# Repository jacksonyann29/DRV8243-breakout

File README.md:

# DRV8243-breakout
 Twin Breakout Board for the Texas Instruments DRV8243 H-bridge Driver intended for driving 2 brushed DC motors.

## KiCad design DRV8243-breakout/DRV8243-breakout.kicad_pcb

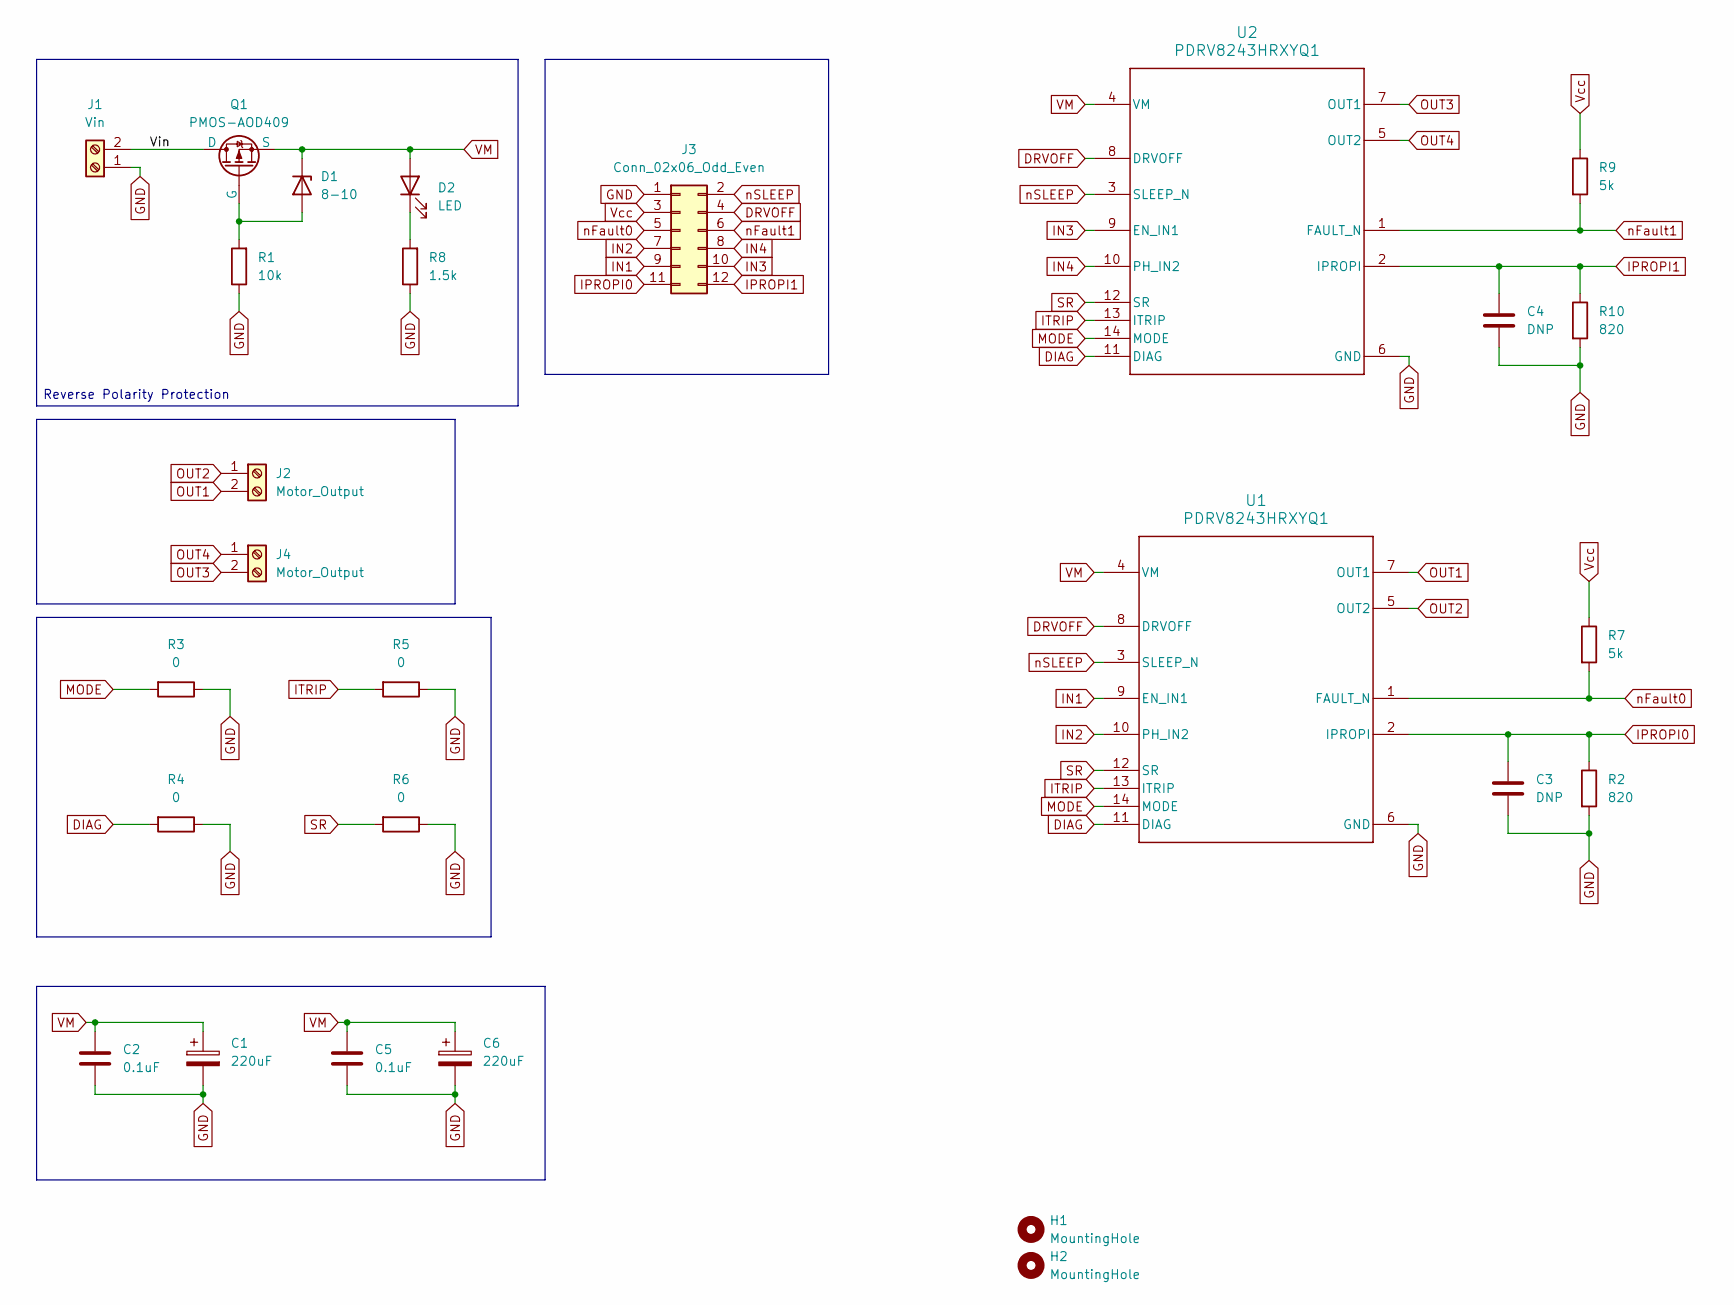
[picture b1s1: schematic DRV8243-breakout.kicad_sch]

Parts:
C1, C6: 220uF; CP_Elec_8x10.5
C2, C5: 0.1uF; C_0603_1608Metric
C3, C4: DNP; C_0805_2012Metric
D1: 8-10; D_SOD-123
D2: LED; LED_0805_2012Metric
H1, H2: MountingHole; MountingHole_3.2mm_M3
J1: Vin; TerminalBlock_Phoenix_MKDS-1,5-2_1x02_P5.00mm_Horizontal
J2, J4: Motor_Output; TerminalBlock_Phoenix_MKDS-1,5-2_1x02_P5.00mm_Horizontal
J3: Conn_02x06_Odd_Even; PinHeader_1x11_P2.54mm_Vertical
Q1: PMOS-AOD409; TO-252-2(DPAK)
R1: 10k; R_0805_2012Metric
R2, R10: 820; R_0805_2012Metric
R3, R4, R5, R6: 0; R_0805_2012Metric
R7, R9: 5k; R_0805_2012Metric
R8: 1.5k; R_0805_2012Metric
U1, U2: PDRV8243HRXYQ1; RXY0014A-MFG

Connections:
/Vin: J1.2, Q1.1 (D)
DIAG: R4.2, U1.11 (DIAG), U2.11 (DIAG)
DRVOFF: J3.4, U1.8 (DRVOFF), U2.8 (DRVOFF)
GND: C1.2, C2.2, C3.2, C4.2, C5.2, C6.2, J1.1, J3.1, R1.1, R2.2, R3.1, R4.1, R5.1, R6.1, R8.1, R10.2, U1.6 (GND), U2.6 (GND)
IN1: J3.9, U1.9 (EN_IN1)
IN2: J3.7, U1.10 (PH_IN2)
IN3: J3.10, U2.9 (EN_IN1)
IN4: J3.8, U2.10 (PH_IN2)
IPROPI0: C3.1, J3.11, R2.1, U1.2 (IPROPI)
IPROPI1: C4.1, J3.12, R10.1, U2.2 (IPROPI)
ITRIP: R5.2, U1.13 (ITRIP), U2.13 (ITRIP)
MODE: R3.2, U1.14 (MODE), U2.14 (MODE)
unnamed: D1.2 (A), Q1.2 (G), R1.2
unnamed: D2.1 (K), R8.2
OUT1: J2.2, U1.7 (OUT1)
OUT2: J2.1, U1.5 (OUT2)
OUT3: J4.2, U2.7 (OUT1)
OUT4: J4.1, U2.5 (OUT2)
SR: R6.2, U1.12 (SR), U2.12 (SR)
VM: C1.1, C2.1, C5.1, C6.1, D1.1 (K), D2.2 (A), Q1.3 (S), U1.4 (VM), U2.4 (VM)
Vcc: J3.3, R7.1, R9.1
nFault0: J3.5, R7.2, U1.1 (FAULT_N)
nFault1: J3.6, R9.2, U2.1 (FAULT_N)
nSLEEP: J3.2, U1.3 (SLEEP_N), U2.3 (SLEEP_N)

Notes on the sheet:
Reverse Polarity Protection

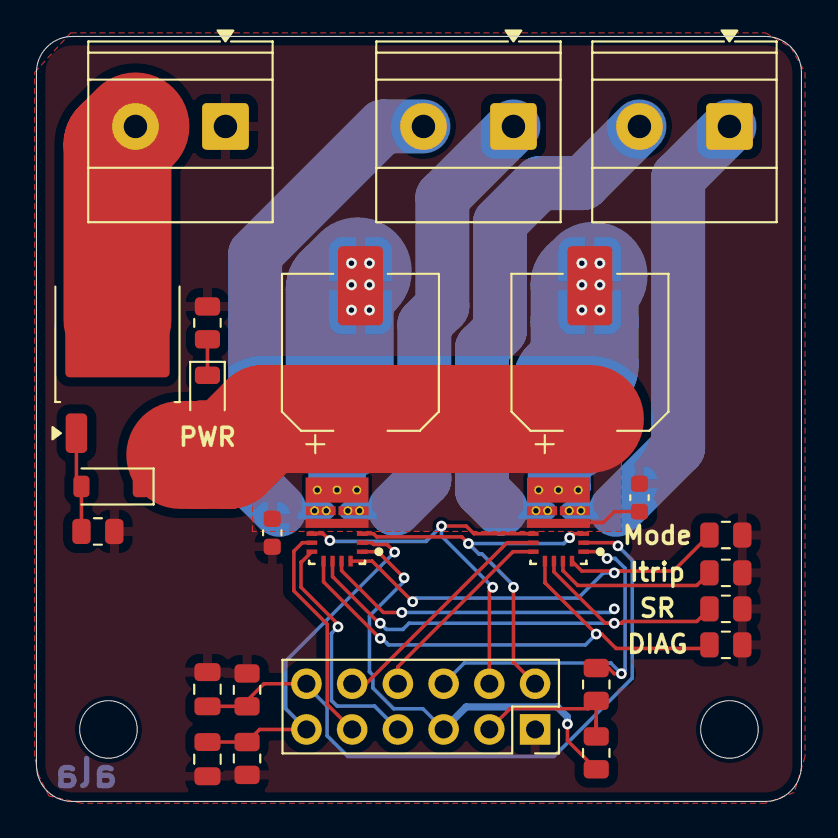
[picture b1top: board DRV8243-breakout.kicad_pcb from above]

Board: 2 copper layers, 42.5 x 42.5 mm, 27 parts (0 on the bottom side), 24 nets.

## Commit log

2025-05-25 Create KiCad Project
2025-05-25 Place DRV8243 Symbol
2025-05-25 Change DRV8243 to hardware varient
2025-05-25 Minimal Setup
2025-05-25 Power Input and protection
2025-05-25 footprints etc
2025-05-25 Layout
2025-05-25 errr
2025-05-29 Fix mosfet footprint
2025-05-29 Add second driver
2025-05-29 layout updates
2025-05-30 Create netclasses and begin routing
2025-05-30 beginning routing
2025-06-04 Update footprint vias
2025-06-04 Initial High Current Routing
2025-06-04 Some more routing
2025-06-04 Update Via placement and associate with pad
2025-06-04 Routing v2
2025-06-04 Routing Etc
2025-06-04 Footprint
2025-06-05 Some Layout Refinement
2025-06-10 Update Silkscreen
